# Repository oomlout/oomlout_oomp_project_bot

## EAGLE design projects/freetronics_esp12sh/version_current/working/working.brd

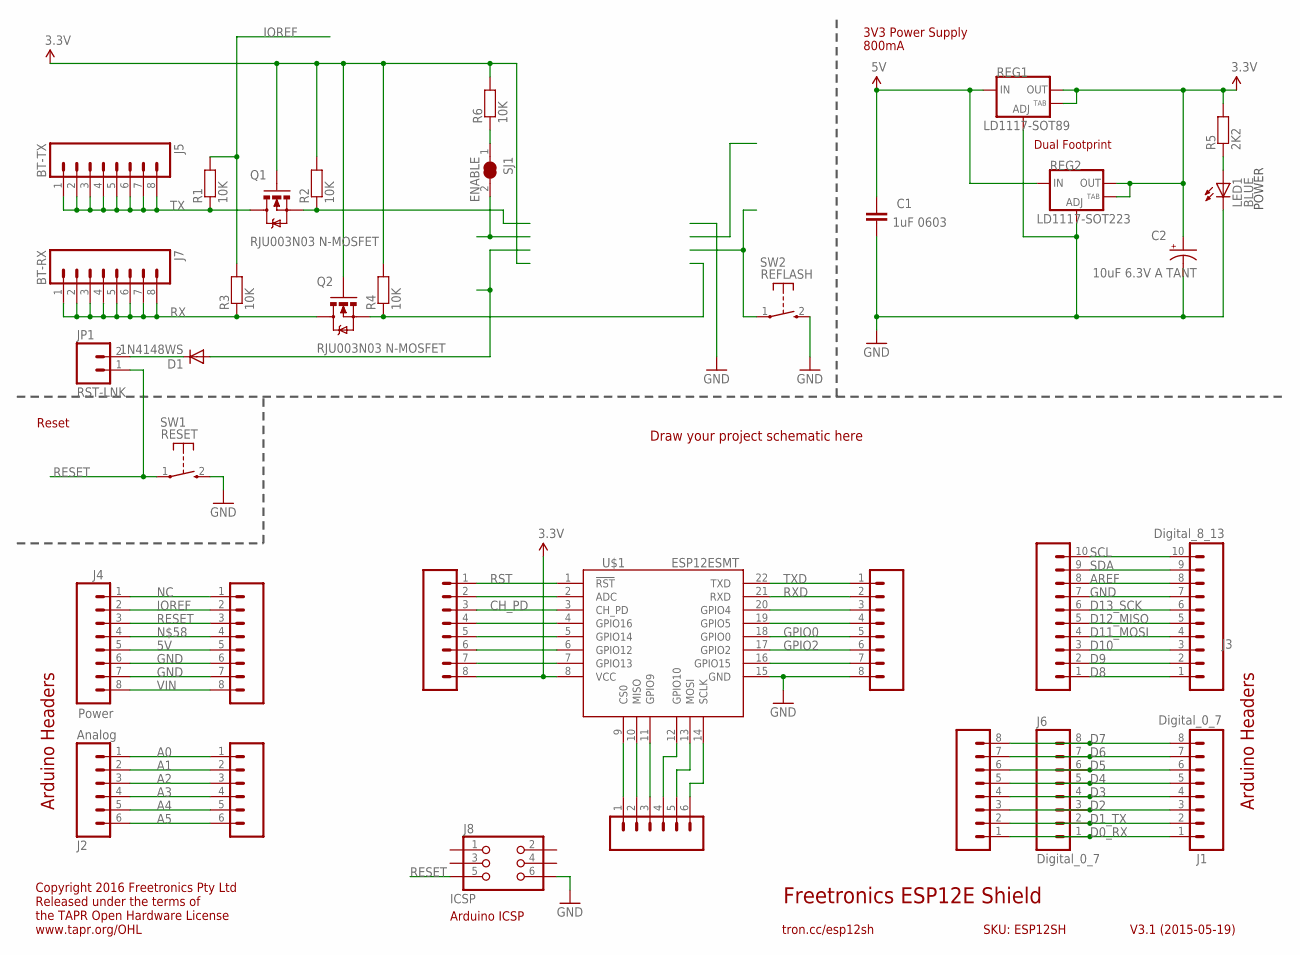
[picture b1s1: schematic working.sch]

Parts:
C1: 1uF 0603; 0603
C2: 10uF 6.3V A TANT; EIA3216
D1: 1N4148WS; SOD-323
J1, J6: Digital_0_7; 1X08
J2: Analog; 1X06
J3: Digital_8_13; 1X10
J4: Power; 1X08
J5: BT-TX; 1X08
J7: BT-RX; 1X08
J8: ICSP; 2X03PTH
JP1: RST-LNK; 1X02
LED1: BLUE; LED-0603
Q1, Q2: RJU003N03 N-MOSFET; SOT32-3
R1, R2, R3, R4, R6: 10K; 0603
R5: 2K2; 0603
REG1: LD1117-SOT89; SOT89
REG2: LD1117-SOT223; SOT223
SJ1: ENABLE; SJC
SL1: Digital_0_7; 1X08
SL2, SL7: Analog; 1X06
SL3: Digital_8_13; 1X10
SL4: Power; 1X08
SL5, SL6: 5V; 1X08
SW1: RESET; TACTILE_SWITCH_SMD_2PIN_TINY
SW2: REFLASH; TACTILE_SWITCH_SMD_2PIN_TINY
U$1: ESP12ESMT; ESP12E

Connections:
3.3V: C2.A (+), Q1.1 (G), Q2.1 (G), R2.2, R4.2, R5.2, R6.2, REG1.2 (OUT), REG1.4 (OUT), REG2.2 (OUT), REG2.4 (OUT), SL6.8, U$1.8 (VCC)
5V: C1.1, J4.5, REG1.3 (IN), REG2.3 (IN), SL4.5
A0: J2.1, SL2.1
A1: J2.2, SL2.2
A2: J2.3, SL2.3
A3: J2.4, SL2.4
A4: J2.5, SL2.5
A5: J2.6, SL2.6
AREF: J3.8, SL3.8
CH_PD: SJ1.2, SL6.3, U$1.3 (CH_PD)
D0_RX: J1.1, J6.1, SL1.1
D1_TX: J1.2, J6.2, SL1.2
D2: J1.3, J6.3, SL1.3
D3: J1.4, J6.4, SL1.4
D4: J1.5, J6.5, SL1.5
D5: J1.6, J6.6, SL1.6
D6: J1.7, J6.7, SL1.7
D7: J1.8, J6.8, SL1.8
D8: J3.1, SL3.1
D9: J3.2, SL3.2
D10: J3.3, SL3.3
D11_MOSI: J3.4, SL3.4
D12_MISO: J3.5, SL3.5
D13_SCK: J3.6, SL3.6
GND: C1.2, C2.C (-), J3.7, J4.6, J4.7, J8.6, LED1.C, REG1.1 (ADJ), REG2.1 (ADJ), SL3.7, SL4.6, SL4.7, SL5.8, SW1.2 (S), SW2.2 (S), U$1.15 (GND)
GPIO0: SL5.5, SW2.1, U$1.18 (GPIO0)
GPIO2: SL5.6, U$1.17 (GPIO2)
IOREF: J4.2, R1.2, R3.2, SL4.2
unnamed: SL7.1, U$1.9 (CS0)
unnamed: SL7.2, U$1.10 (MISO)
unnamed: SL7.3, U$1.11 (GPIO9)
unnamed: SL7.4, U$1.12 (GPIO10)
unnamed: LED1.A, R5.1
unnamed: SL7.5, U$1.13 (MOSI)
unnamed: SL7.6, U$1.14 (SCLK)
unnamed: SL5.7, U$1.16 (GPIO15)
unnamed: SL5.4, U$1.19 (GPIO5)
unnamed: SL5.3, U$1.20 (GPIO4)
unnamed: SL6.2, U$1.2 (ADC)
unnamed: SL6.4, U$1.4 (GPIO16)
unnamed: SL6.5, U$1.5 (GPIO14)
unnamed: SL6.6, U$1.6 (GPIO12)
unnamed: SL6.7, U$1.7 (GPIO13)
unnamed: J4.4, SL4.4
unnamed: R6.1, SJ1.1
unnamed: D1.1 (C), JP1.2
NC: J4.1, SL4.1
RESET: J4.3, J8.5, JP1.1, SL4.3, SW1.1
RST: D1.2 (A), SL6.1, U$1.1 (!RST)
RX: J7.1, J7.2, J7.3, J7.4, J7.5, J7.6, J7.7, J7.8, Q2.3 (D), R3.1
RXD: Q2.2 (S), R4.1, SL5.2, U$1.21 (RXD)
SCL: J3.10, SL3.10
SDA: J3.9, SL3.9
TX: J5.1, J5.2, J5.3, J5.4, J5.5, J5.6, J5.7, J5.8, Q1.3 (D), R1.1
TXD: Q1.2 (S), R2.1, SL5.1, U$1.22 (TXD)
VIN: J4.8, SL4.8

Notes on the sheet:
Freetronics ESP12E Shield
V3.1 (2015-05-19)
tron.cc/esp12sh
SKU: ESP12SH
Arduino Headers
Reset
Draw your project schematic here
Arduino ICSP
Copyright 2016 Freetronics Pty Ltd Released under the terms of the TAPR Open Hardware License www.tapr.org/OHL
POWER
3V3 Power Supply
Dual Footprint
800mA

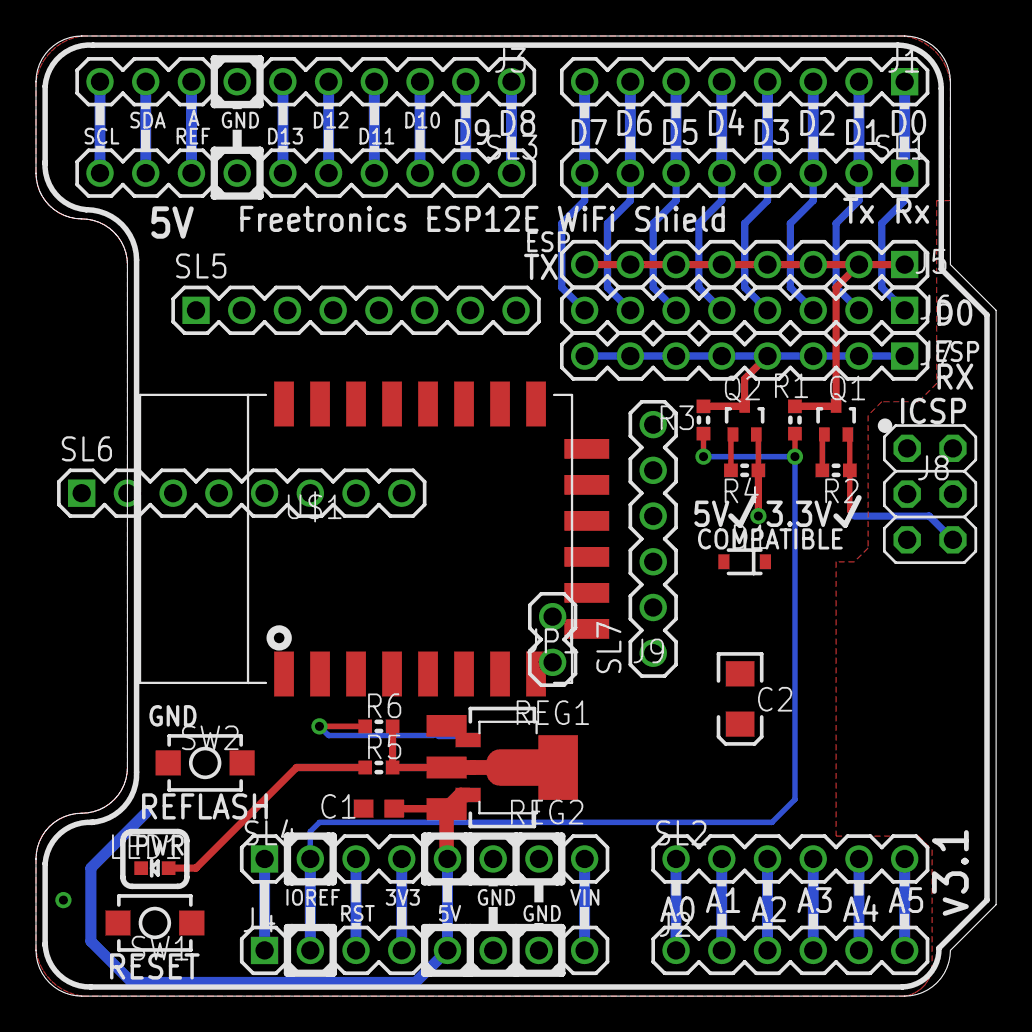
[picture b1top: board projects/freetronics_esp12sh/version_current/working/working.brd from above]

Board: 2 copper layers, 53.3 x 53.3 mm, 34 parts (1 on the bottom side), 56 nets.

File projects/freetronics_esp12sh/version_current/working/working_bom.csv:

"Id";"Designator";"Footprint";"Quantity";"Designation";"Supplier and ref";
1;"R3,R6,R1,R4,R2";"0603";5;"10K";;;
2;"SL6,SL5";"1X08";2;"5V";;;
3;"J2,SL2,SL7";"1X06";3;"Analog";;;
4;"R5";"0603";1;"2K2";;;
5;"J4,SL4";"1X08";2;"Power";;;
6;"C2";"EIA3216";1;"10uF 6.3V A TANT";;;
7;"SW2";"TACTILE_SWITCH_SMD_2PIN_TINY";1;"REFLASH";;;
8;"Q1,Q2";"SOT32-3";2;"RJU003N03 N-MOSFET";;;
9;"JP1";"1X02";1;"RST-LNK";;;
10;"J3,SL3";"1X10";2;"Digital_8_13";;;
11;"J1,SL1,J6";"1X08";3;"Digital_0_7";;;
12;"U$1";"ESP12E";1;"ESP12ESMT";;;
13;"REG1";"SOT89";1;"LD1117-SOT89";;;
14;"J5";"1X08";1;"BT-TX";;;
15;"D1";"SOD-323";1;"1N4148WS";;;
16;"C1";"0603";1;"1uF 0603";;;
17;"J8";"2X03PTH";1;"ICSP";;;
18;"SW1";"TACTILE_SWITCH_SMD_2PIN_TINY";1;"RESET";;;
19;"J7";"1X08";1;"BT-RX";;;
20;"LED1";"LED-0603";1;"BLUE";;;
21;"REG2";"SOT223";1;"LD1117-SOT223";;;
22;"SJ1";"SJC";1;"ENABLE";;;

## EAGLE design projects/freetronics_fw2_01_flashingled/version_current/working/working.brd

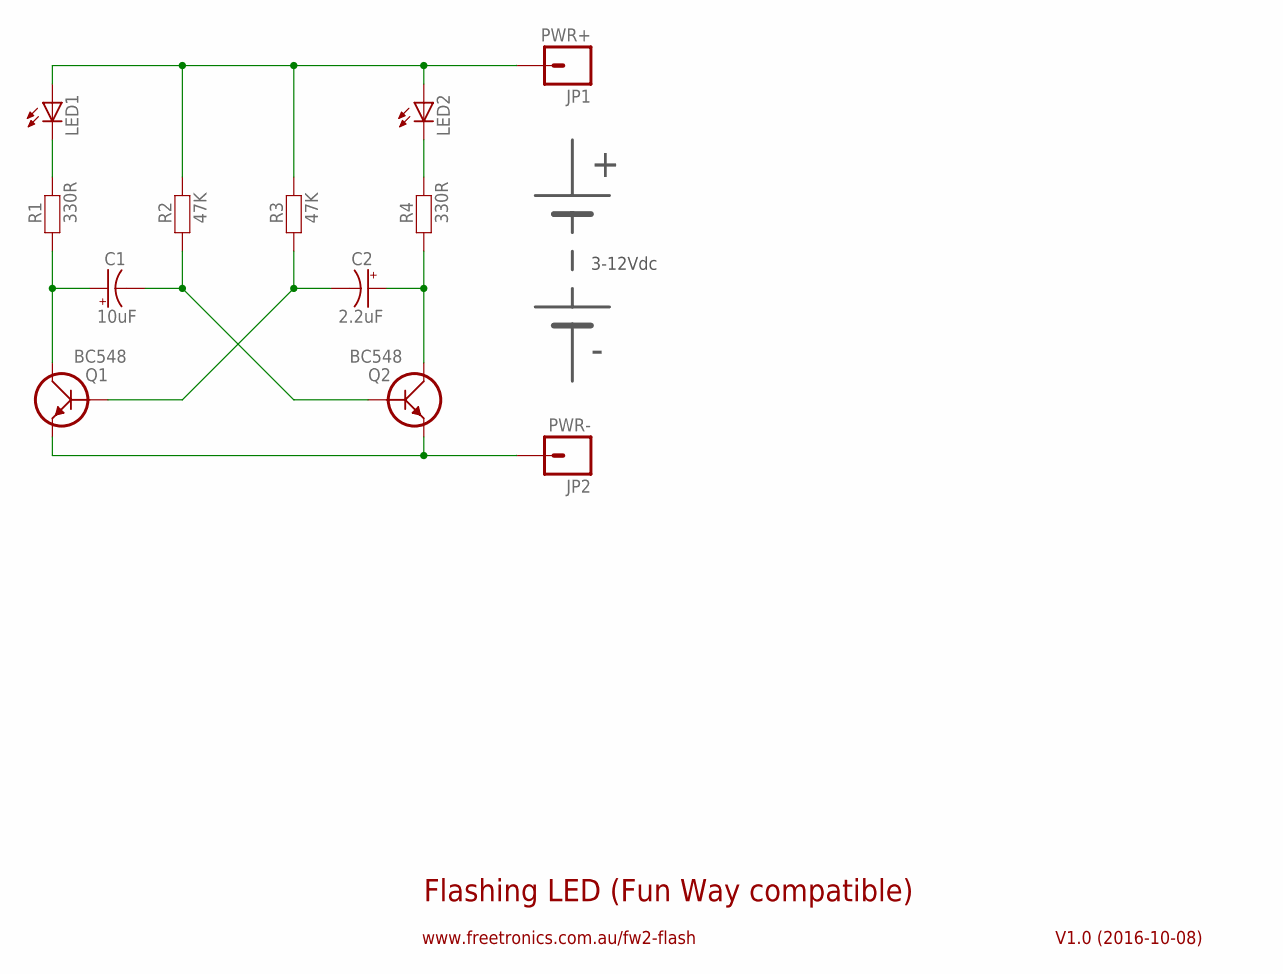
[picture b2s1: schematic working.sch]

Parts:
C1: 10uF; E5-5
C2: 2.2uF; E5-5
JP1: PWR+; 1X01
JP2: PWR-; 1X01
LED1, LED2: LED5MML; LED5MMLARGE
Q1, Q2: BC548; TO-92
R1, R4: 330R; AXIAL-0.4-LARGE
R2, R3: 47K; AXIAL-0.4-LARGE

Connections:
unnamed: LED1.K (C), R1.P$2 (2)
unnamed: JP1.1, LED1.A, LED2.A, R2.P$2 (2), R3.P$2 (2)
unnamed: C1.+, Q1.1 (C), R1.P$1 (1)
unnamed: C2.+, Q2.1 (C), R4.P$1 (1)
unnamed: LED2.K (C), R4.P$2 (2)
unnamed: C2.-, Q1.2 (B), R3.P$1 (1)
unnamed: C1.-, Q2.2 (B), R2.P$1 (1)
unnamed: JP2.1, Q1.3 (E), Q2.3 (E)

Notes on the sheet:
Flashing LED (Fun Way compatible)
V1.0 (2016-10-08)
www.freetronics.com.au/fw2-flash
3-12Vdc

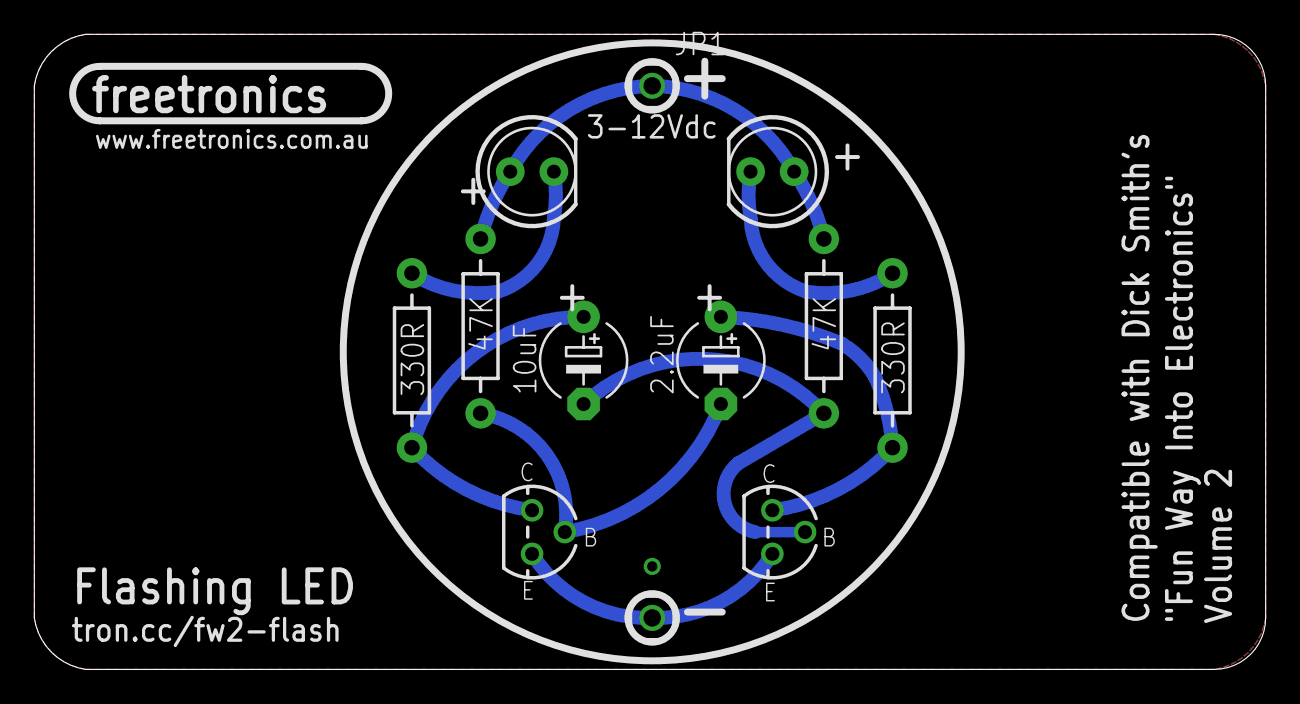
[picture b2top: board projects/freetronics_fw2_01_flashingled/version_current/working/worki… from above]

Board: 2 copper layers, 71.7 x 37.0 mm, 12 parts (0 on the bottom side), 8 nets.

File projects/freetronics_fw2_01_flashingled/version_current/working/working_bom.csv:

"Id";"Designator";"Footprint";"Quantity";"Designation";"Supplier and ref";
1;"C1";"E5-5";1;"10uF";;;
2;"Q1,Q2";"TO-92";2;"BC548";;;
3;"R3,R2";"AXIAL-0.4-LARGE";2;"47K";;;
4;"R4,R1";"AXIAL-0.4-LARGE";2;"330R";;;
5;"LED1,LED2";"LED5MMLARGE";2;"";;;
6;"JP1";"1X01";1;"PWR+";;;
7;"C2";"E5-5";1;"2.2uF";;;
8;"JP2";"1X01";1;"PWR-";;;

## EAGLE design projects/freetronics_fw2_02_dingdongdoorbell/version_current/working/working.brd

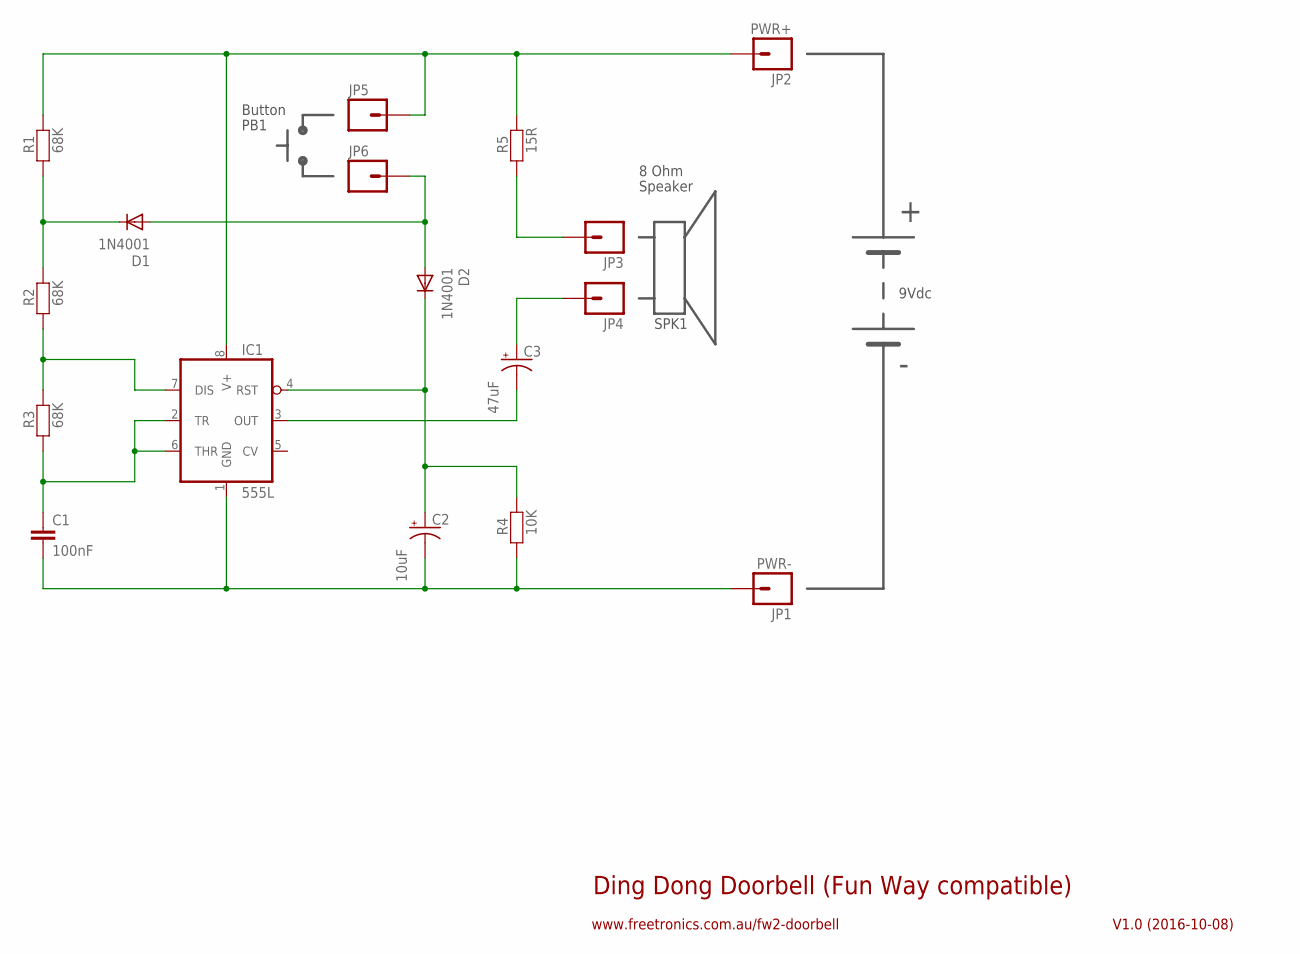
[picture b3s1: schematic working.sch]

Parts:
C1: 100nF; CAP-PTH-SMALL
C2: 10uF; CPOL-RADIAL-10UF-25V
C3: 47uF; CPOL-RADIAL-10UF-25V
D1, D2: 1N4001; DIODE-1N4001
IC1: 555L; DIL08L
JP1, JP5, JP6: PWR-; 1X01
JP2: PWR+; 1X01
JP3: SPKR+; 1X01
JP4: SPKR-; 1X01
R1, R2, R3: 68K; AXIAL-0.4-LARGE
R4: 10K; AXIAL-0.4-LARGE
R5: 15R; AXIAL-0.4-LARGE

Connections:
unnamed: D1.C, R1.P$1 (1), R2.P$2 (2)
unnamed: IC1.7 (DIS), R2.P$1 (1), R3.P$2 (2)
unnamed: D1.A, D2.A, JP6.1
unnamed: IC1.8 (V+), JP2.1, JP5.1, R1.P$2 (2), R5.P$2 (2)
unnamed: JP3.1, R5.P$1 (1)
unnamed: C3.1 (+), JP4.1
unnamed: C3.2 (-), IC1.3 (OUT)
unnamed: C2.1 (+), D2.C, IC1.4 (RST), R4.P$2 (2)
unnamed: C1.2, C2.2 (-), IC1.1 (GND), JP1.1, R4.P$1 (1)
unnamed: C1.1, IC1.2 (TR), IC1.6 (THR), R3.P$1 (1)

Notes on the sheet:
Ding Dong Doorbell (Fun Way compatible)
V1.0 (2016-10-08)
www.freetronics.com.au/fw2-doorbell
9Vdc
8 Ohm
Speaker
Button
PB1
SPK1

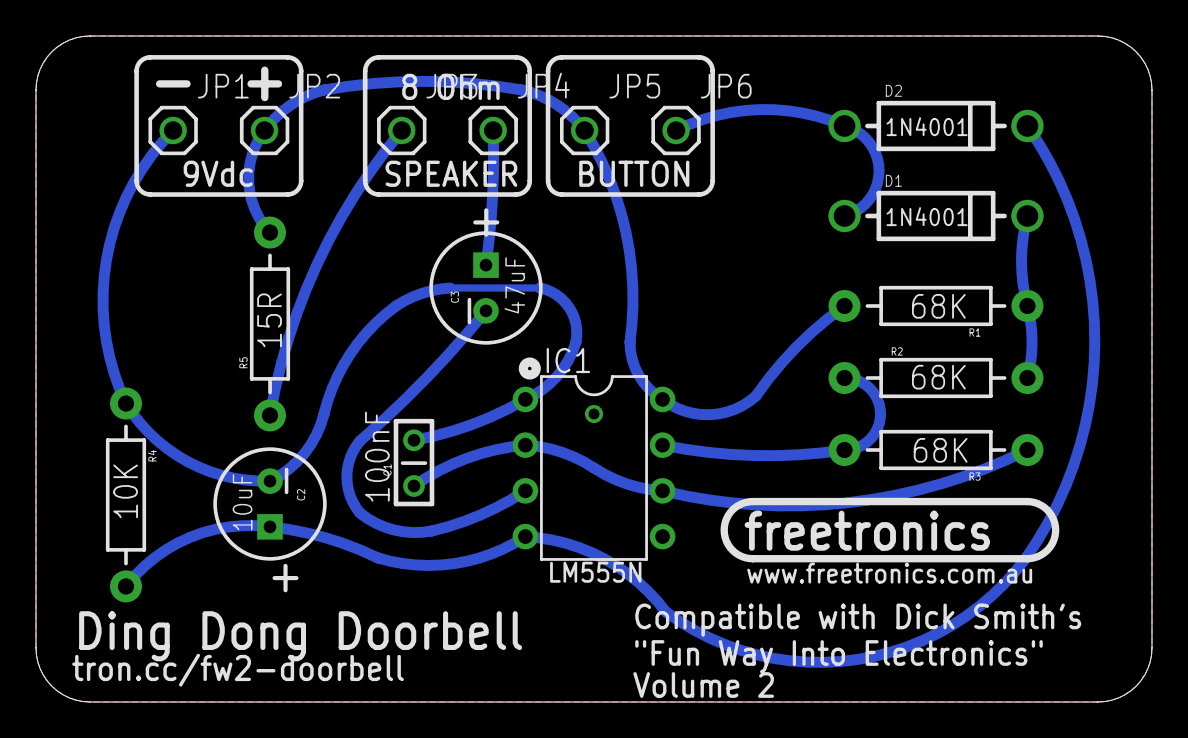
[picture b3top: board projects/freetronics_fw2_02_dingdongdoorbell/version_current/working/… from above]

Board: 2 copper layers, 62.0 x 37.0 mm, 17 parts (0 on the bottom side), 10 nets.

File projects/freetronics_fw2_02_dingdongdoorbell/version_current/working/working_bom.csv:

"Id";"Designator";"Footprint";"Quantity";"Designation";"Supplier and ref";
1;"JP5,JP1,JP6";"1X01";3;"PWR-";;;
2;"C2";"CPOL-RADIAL-10UF-25V";1;"10uF";;;
3;"D2,D1";"DIODE-1N4001";2;"1N4001";;;
4;"C1";"CAP-PTH-SMALL";1;"100nF";;;
5;"IC1";"DIL08L";1;"555L";;;
6;"JP3";"1X01";1;"SPKR+";;;
7;"JP2";"1X01";1;"PWR+";;;
8;"R3,R1,R2";"AXIAL-0.4-LARGE";3;"68K";;;
9;"C3";"CPOL-RADIAL-10UF-25V";1;"47uF";;;
10;"JP4";"1X01";1;"SPKR-";;;
11;"R5";"AXIAL-0.4-LARGE";1;"15R";;;
12;"R4";"AXIAL-0.4-LARGE";1;"10K";;;

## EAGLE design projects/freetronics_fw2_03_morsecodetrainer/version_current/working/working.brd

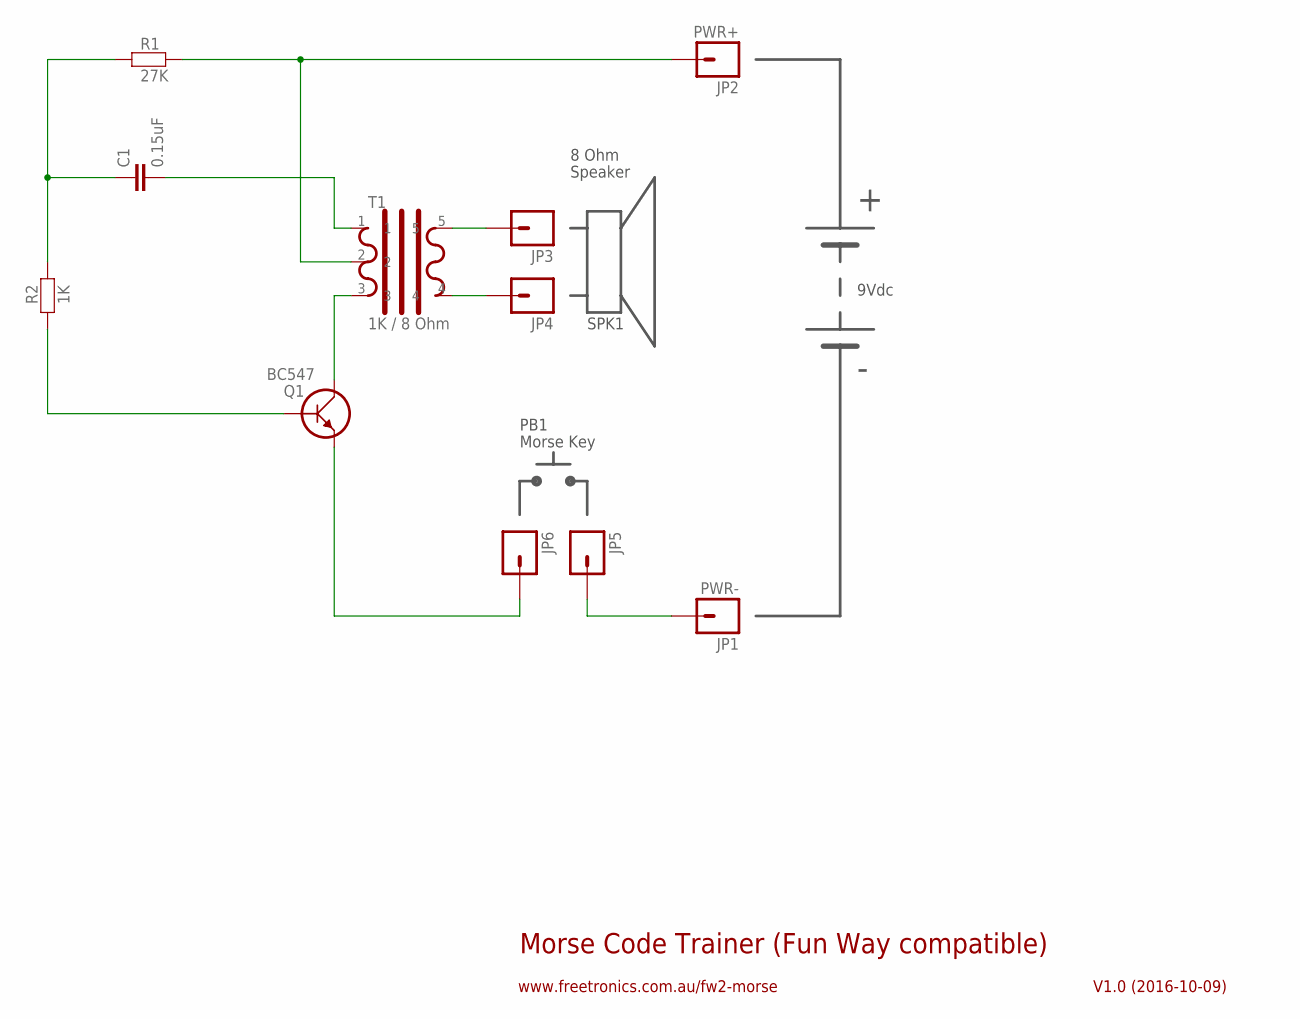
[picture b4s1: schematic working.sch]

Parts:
C1: 0.15uF; CAP-PTH-SMALL
JP1, JP5, JP6: PWR-; 1X01
JP2: PWR+; 1X01
JP3: SPKR+; 1X01
JP4: SPKR-; 1X01
Q1: BC547; TO-92
R1: 27K; FREETRONICS_AXIAL-0.4
R2: 1K; FREETRONICS_AXIAL-0.4
T1: 1K / 8 Ohm; TRANS350MW

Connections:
unnamed: JP4.1, T1.4
unnamed: JP3.1, T1.5
unnamed: JP2.1, R1.P$2 (2), T1.2
unnamed: C1.2, T1.1
unnamed: Q1.1 (C), T1.3
unnamed: JP1.1, JP5.1
unnamed: JP6.1, Q1.3 (E)
unnamed: Q1.2 (B), R2.P$1 (1)
unnamed: C1.1, R1.P$1 (1), R2.P$2 (2)

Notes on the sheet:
Morse Code Trainer (Fun Way compatible)
V1.0 (2016-10-09)
www.freetronics.com.au/fw2-morse
9Vdc
8 Ohm
Speaker
Morse Key
PB1
SPK1

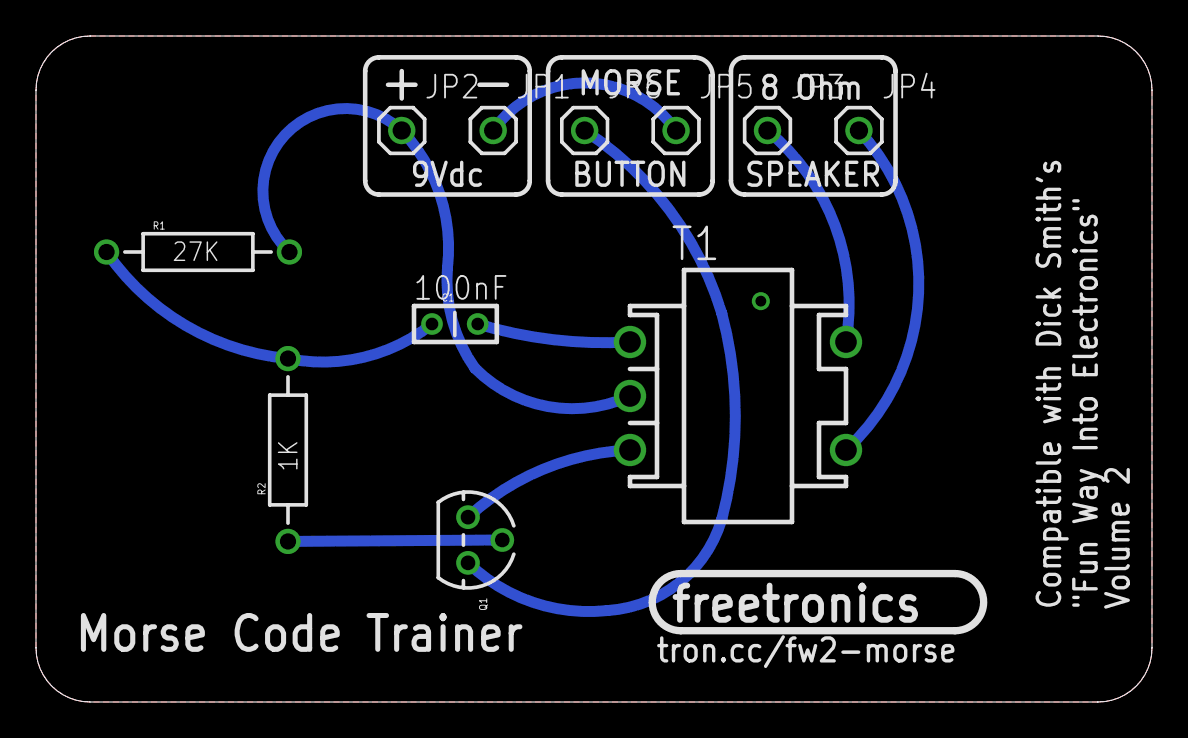
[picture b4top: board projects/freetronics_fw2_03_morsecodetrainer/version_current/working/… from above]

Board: 2 copper layers, 62.0 x 37.0 mm, 11 parts (0 on the bottom side), 9 nets.

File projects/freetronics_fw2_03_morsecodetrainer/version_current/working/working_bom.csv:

"Id";"Designator";"Footprint";"Quantity";"Designation";"Supplier and ref";
1;"JP3";"1X01";1;"SPKR+";;;
2;"T1";"TRANS350MW";1;"1K / 8 Ohm";;;
3;"JP2";"1X01";1;"PWR+";;;
4;"C1";"CAP-PTH-SMALL";1;"0.15uF";;;
5;"R2";"FREETRONICS_AXIAL-0.4";1;"1K";;;
6;"R1";"FREETRONICS_AXIAL-0.4";1;"27K";;;
7;"Q1";"TO-92";1;"BC547";;;
8;"JP6,JP5,JP1";"1X01";3;"PWR-";;;
9;"JP4";"1X01";1;"SPKR-";;;

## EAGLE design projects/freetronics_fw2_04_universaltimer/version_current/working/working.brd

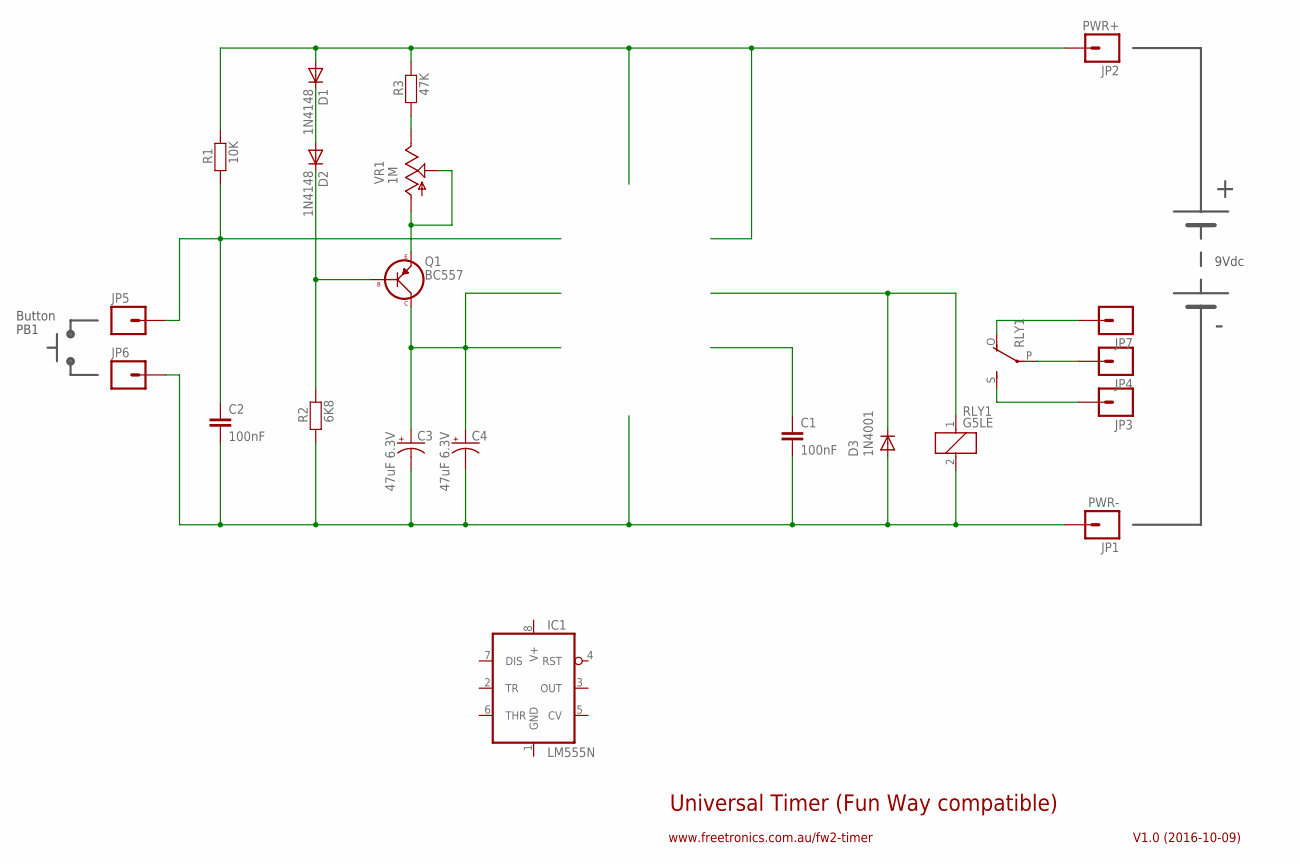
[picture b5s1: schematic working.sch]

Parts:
C1, C2: 100nF; CAP-PTH-SMALL
C3, C4: 47uF 6.3V; CPOL-RADIAL-10UF-25V
D1, D2: 1N4148; DIODE-1N914
D3: 1N4001; DIODE-1N4001
IC1: LM555N; DIL08
JP1, JP5, JP6: PWR-; 1X01
JP2: PWR+; 1X01
JP3: SPKR+; 1X01
JP4, JP7: SPKR-; 1X01
Q1: BC557; TO-92
R1: 10K; FREETRONICS_AXIAL-0.4
R2: 6K8; FREETRONICS_AXIAL-0.4
R3: 47K; FREETRONICS_AXIAL-0.4
RLY1: G5LE
VR1: 1M; 6MM

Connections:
GND: IC1.1 (GND)
unnamed: C3.1 (+), C4.1 (+), Q1.1 (C)
unnamed: C1.2, C2.2, C3.2 (-), C4.2 (-), D3.A, JP1.1, JP6.1, R2.P$1 (1), RLY1.2
unnamed: D3.C, RLY1.1
unnamed: JP4.1, RLY1.P
unnamed: JP3.1, RLY1.S
unnamed: JP7.1, RLY1.O
unnamed: C2.1, JP5.1, R1.P$1 (1)
unnamed: D2.C, Q1.2 (B), R2.P$2 (2)
unnamed: Q1.3 (E), VR1.A, VR1.S
unnamed: D1.A, JP2.1, R1.P$2 (2), R3.P$2 (2)
unnamed: R3.P$1 (1), VR1.E
unnamed: D1.C, D2.A
V+: IC1.8 (V+)

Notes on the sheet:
Universal Timer (Fun Way compatible)
V1.0 (2016-10-09)
www.freetronics.com.au/fw2-timer
9Vdc
Button
PB1

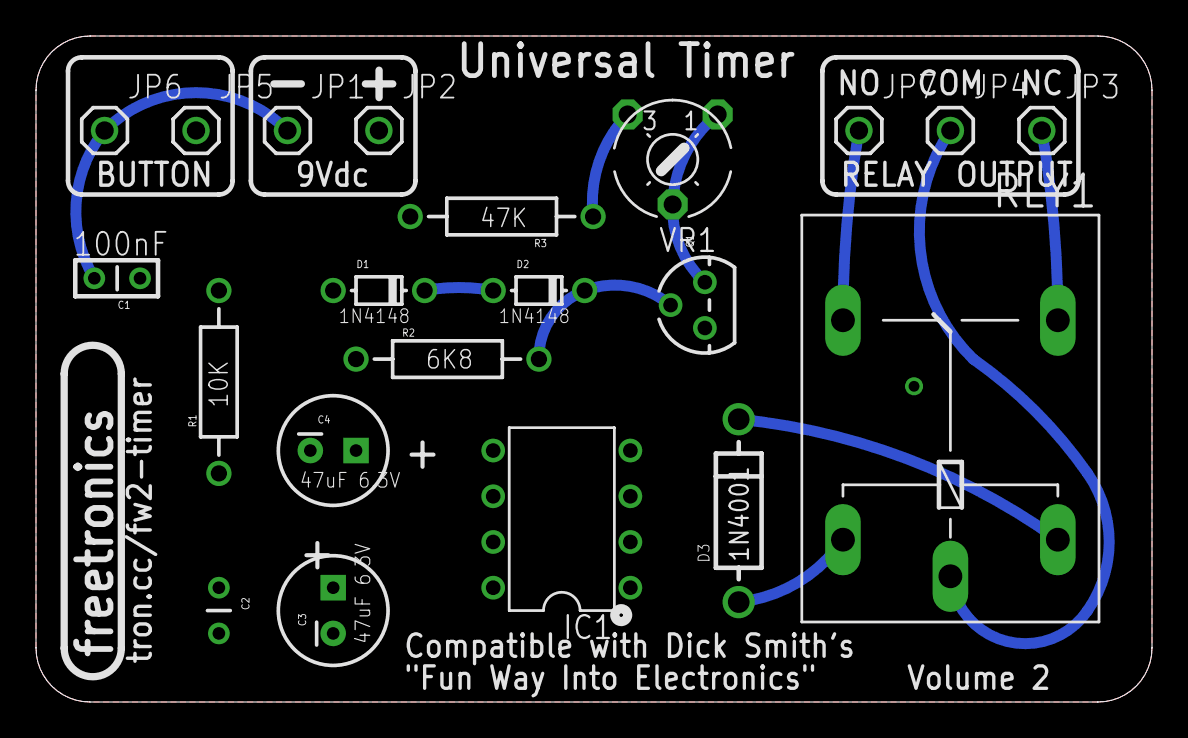
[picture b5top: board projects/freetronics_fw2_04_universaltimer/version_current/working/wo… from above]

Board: 2 copper layers, 62.0 x 37.0 mm, 21 parts (0 on the bottom side), 12 nets.

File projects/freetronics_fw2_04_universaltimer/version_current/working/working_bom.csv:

"Id";"Designator";"Footprint";"Quantity";"Designation";"Supplier and ref";
1;"C1,C2";"CAP-PTH-SMALL";2;"100nF";;;
2;"JP6,JP5,JP1";"1X01";3;"PWR-";;;
3;"D3";"DIODE-1N4001";1;"1N4001";;;
4;"JP2";"1X01";1;"PWR+";;;
5;"D1,D2";"DIODE-1N914";2;"1N4148";;;
6;"JP3";"1X01";1;"SPKR+";;;
7;"VR1";"6MM";1;"1M";;;
8;"JP4,JP7";"1X01";2;"SPKR-";;;
9;"R3";"FREETRONICS_AXIAL-0.4";1;"47K";;;
10;"R2";"FREETRONICS_AXIAL-0.4";1;"6K8";;;
11;"C3,C4";"CPOL-RADIAL-10UF-25V";2;"47uF 6.3V";;;
12;"IC1";"DIL08";1;"LM555N";;;
13;"R1";"FREETRONICS_AXIAL-0.4";1;"10K";;;
14;"Q1";"TO-92";1;"BC557";;;
15;"RLY1";"G5LE";1;"G5LE";;;

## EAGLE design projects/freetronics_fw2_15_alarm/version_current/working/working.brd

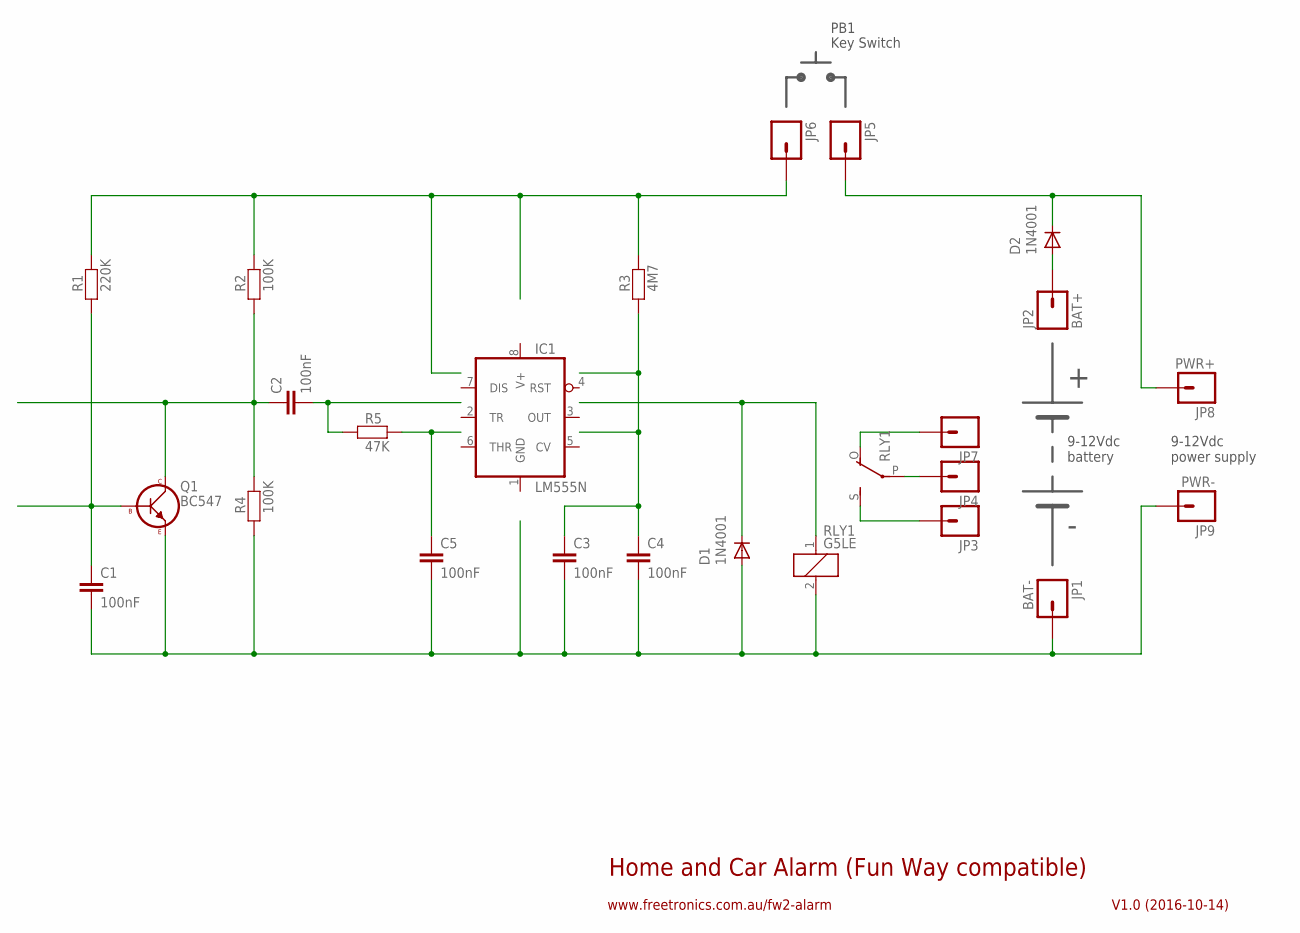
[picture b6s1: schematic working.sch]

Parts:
C1, C2, C3, C4, C5: 100nF; CAP-PTH-SMALL
D1, D2: 1N4001; DIODE-1N4001
IC1: LM555N; DIL08
JP1: BAT-; 1X01
JP2: BAT+; 1X01
JP3: SPKR+; 1X01
JP4, JP7: SPKR-; 1X01
JP5, JP6, JP9: PWR-; 1X01
JP8: PWR+; 1X01
Q1: BC547; TO-92
R1: 220K; FREETRONICS_AXIAL-0.4
R2, R4: 100K; FREETRONICS_AXIAL-0.4
R3: 4M7; FREETRONICS_AXIAL-0.4
R5: 47K; FREETRONICS_AXIAL-0.4
RLY1: G5LE

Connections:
GND: IC1.1 (GND)
unnamed: C3.1, C4.1, R3.P$1 (1)
unnamed: C1.2, C3.2, C4.2, C5.2, D1.A, JP1.1, JP9.1, Q1.3 (E), R4.P$1 (1), RLY1.2
unnamed: D1.C, RLY1.1
unnamed: JP6.1, R1.P$2 (2), R2.P$2 (2), R3.P$2 (2)
unnamed: JP4.1, RLY1.P
unnamed: JP3.1, RLY1.S
unnamed: JP7.1, RLY1.O
unnamed: C5.1, R5.P$2 (2)
unnamed: C1.1, Q1.2 (B), R1.P$1 (1)
unnamed: C2.1, Q1.1 (C), R2.P$1 (1), R4.P$2 (2)
unnamed: C2.2, R5.P$1 (1)
unnamed: D2.A, JP2.1
unnamed: D2.C, JP5.1, JP8.1
V+: IC1.8 (V+)

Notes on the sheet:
Home and Car Alarm (Fun Way compatible)
V1.0 (2016-10-14)
www.freetronics.com.au/fw2-alarm
9-12Vdc battery
Key Switch
PB1
9-12Vdc power supply

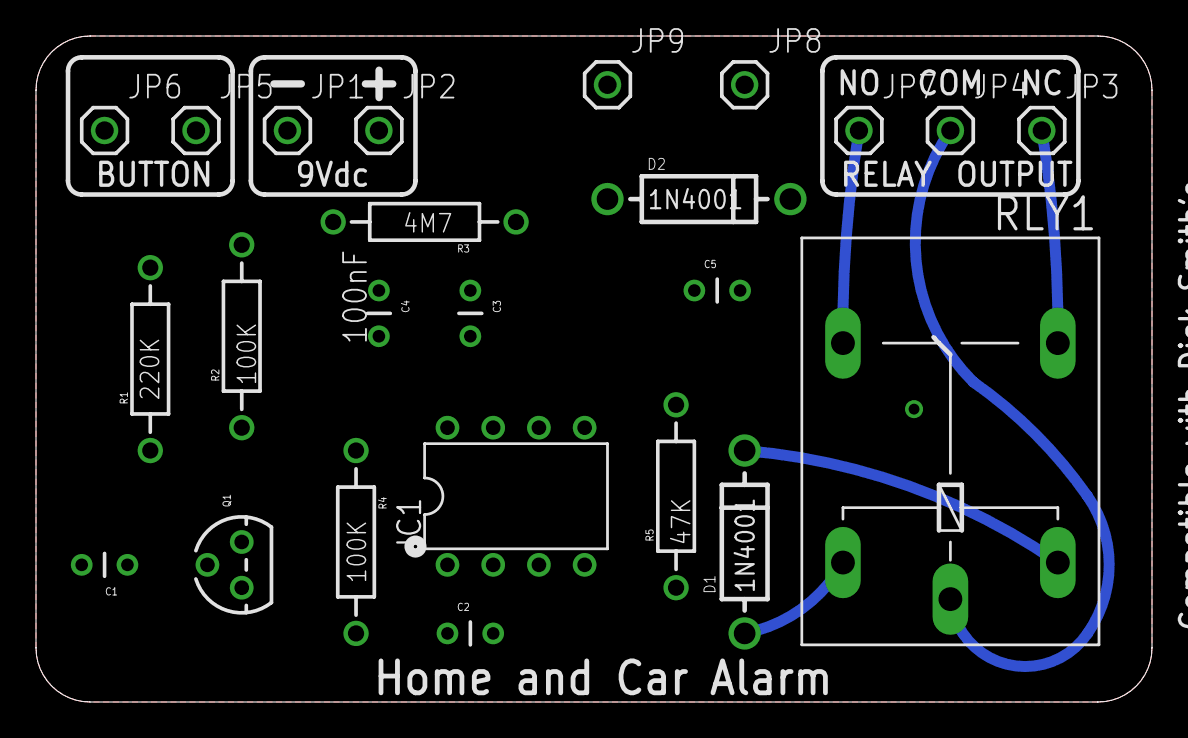
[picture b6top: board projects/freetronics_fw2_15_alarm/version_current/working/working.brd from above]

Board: 2 copper layers, 62.0 x 37.0 mm, 24 parts (0 on the bottom side), 13 nets.

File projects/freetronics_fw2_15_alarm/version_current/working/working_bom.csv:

"Id";"Designator";"Footprint";"Quantity";"Designation";"Supplier and ref";
1;"R3";"FREETRONICS_AXIAL-0.4";1;"4M7";;;
2;"JP5,JP9,JP6";"1X01";3;"PWR-";;;
3;"C2,C4,C1,C5,C3";"CAP-PTH-SMALL";5;"100nF";;;
4;"R2,R4";"FREETRONICS_AXIAL-0.4";2;"100K";;;
5;"R1";"FREETRONICS_AXIAL-0.4";1;"220K";;;
6;"JP7,JP4";"1X01";2;"SPKR-";;;
7;"JP1";"1X01";1;"BAT-";;;
8;"JP3";"1X01";1;"SPKR+";;;
9;"IC1";"DIL08";1;"LM555N";;;
10;"R5";"FREETRONICS_AXIAL-0.4";1;"47K";;;
11;"Q1";"TO-92";1;"BC547";;;
12;"D2,D1";"DIODE-1N4001";2;"1N4001";;;
13;"JP2";"1X01";1;"BAT+";;;
14;"RLY1";"G5LE";1;"G5LE";;;
15;"JP8";"1X01";1;"PWR+";;;

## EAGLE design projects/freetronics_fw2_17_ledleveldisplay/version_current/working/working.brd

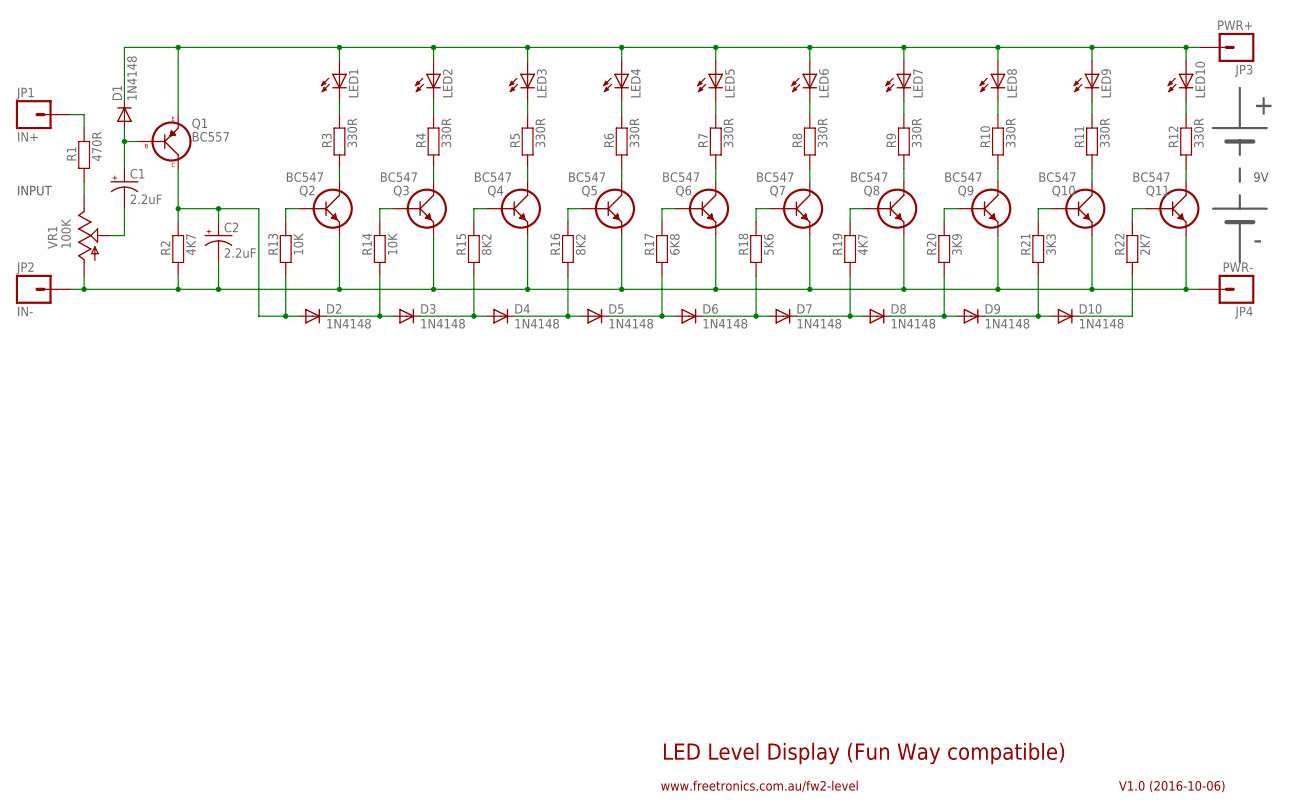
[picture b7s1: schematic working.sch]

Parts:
C1, C2: 2.2uF; CPOL-RADIAL-100UF-25V
D1, D2, D3, D4, D5, D6, D7, D8, D9, D10: 1N4148; DIODE-1N914L
JP1: IN+; 1X01
JP2: IN-; 1X01
JP3: PWR+; 1X01
JP4: PWR-; 1X01
LED1, LED2, LED3, LED4, LED5, LED6, LED7, LED8, LED9, LED10: LED5MML; LED5MMLARGE
Q1: BC557; TO-92
Q2, Q3, Q4, Q5, Q6, Q7, Q8, Q9, Q10, Q11: BC547; TO-92
R1: 470R; AXIAL-0.4-LARGE
R2: 4K7; AXIAL-0.4-LARGE
R3, R4, R5, R6, R7, R8, R9, R10, R11, R12: 330R; 0309VW
R13, R14: 10K; 0309VW
R15, R16: 8K2; 0309VW
R17: 6K8; 0309VW
R18: 5K6; 0309VW
R19: 4K7; 0309VW
R20: 3K9; 0309VW
R21: 3K3; 0309VW
R22: 2K7; 0309VW
VR1: 100K; 6MM

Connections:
unnamed: D10.C, R22.1
unnamed: Q2.2 (B), R13.2
unnamed: Q2.1 (C), R3.2
unnamed: LED1.K (C), R3.1
unnamed: Q11.2 (B), R22.2
unnamed: D1.C, JP3.1, LED1.A, LED2.A, LED3.A, LED4.A, LED5.A, LED6.A, LED7.A, LED8.A, LED9.A, LED10.A, Q1.3 (E)
unnamed: Q3.1 (C), R4.2
unnamed: LED2.K (C), R4.1
unnamed: Q4.1 (C), R5.2
unnamed: D6.C, D7.A, R18.1
unnamed: LED3.K (C), R5.1
unnamed: Q3.2 (B), R14.2
unnamed: C2.1 (+), D2.A, Q1.1 (C), R2.P$2 (2), R13.1
unnamed: D2.C, D3.A, R14.1
unnamed: C2.2 (-), JP2.1, JP4.1, Q2.3 (E), Q3.3 (E), Q4.3 (E), Q5.3 (E), Q6.3 (E), Q7.3 (E), Q8.3 (E), Q9.3 (E), Q10.3 (E), Q11.3 (E), R2.P$1 (1), VR1.A
unnamed: Q5.1 (C), R6.2
unnamed: LED4.K (C), R6.1
unnamed: Q6.1 (C), R7.2
unnamed: LED5.K (C), R7.1
unnamed: Q7.1 (C), R8.2
unnamed: LED6.K (C), R8.1
unnamed: Q4.2 (B), R15.2
unnamed: Q5.2 (B), R16.2
unnamed: Q6.2 (B), R17.2
unnamed: D5.C, D6.A, R17.1
unnamed: D4.C, D5.A, R16.1
unnamed: D3.C, D4.A, R15.1
unnamed: D7.C, D8.A, R19.1
unnamed: D8.C, D9.A, R20.1
unnamed: D9.C, D10.A, R21.1
unnamed: Q7.2 (B), R18.2
unnamed: Q8.2 (B), R19.2
unnamed: Q9.2 (B), R20.2
unnamed: Q10.2 (B), R21.2
unnamed: Q8.1 (C), R9.2
unnamed: LED7.K (C), R9.1
unnamed: Q9.1 (C), R10.2
unnamed: LED8.K (C), R10.1
unnamed: Q10.1 (C), R11.2
unnamed: LED9.K (C), R11.1
unnamed: Q11.1 (C), R12.2
unnamed: LED10.K (C), R12.1
unnamed: C1.1 (+), D1.A, Q1.2 (B)
unnamed: C1.2 (-), VR1.S
unnamed: R1.P$1 (1), VR1.E
unnamed: JP1.1, R1.P$2 (2)

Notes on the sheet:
LED Level Display (Fun Way compatible)
V1.0 (2016-10-06)
www.freetronics.com.au/fw2-level
INPUT

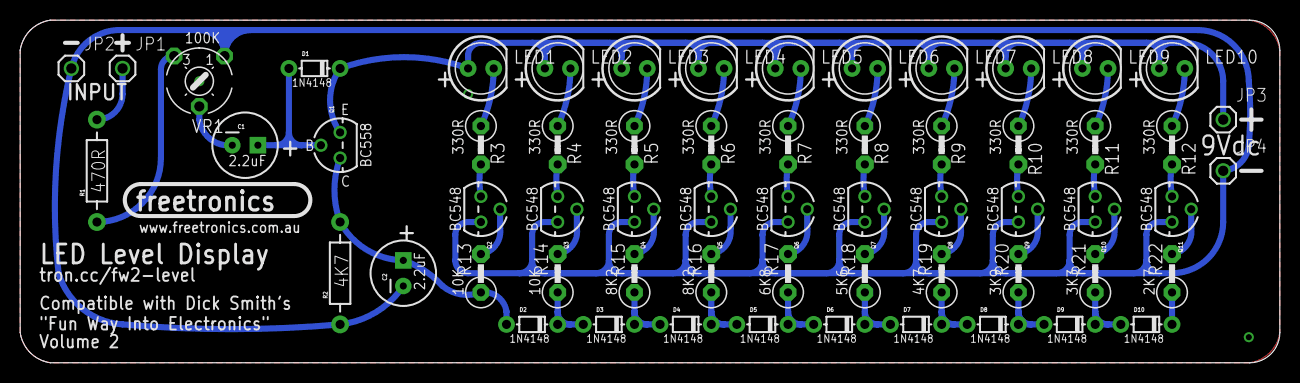
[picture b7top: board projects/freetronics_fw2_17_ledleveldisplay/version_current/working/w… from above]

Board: 2 copper layers, 125.0 x 34.0 mm, 60 parts (0 on the bottom side), 46 nets.

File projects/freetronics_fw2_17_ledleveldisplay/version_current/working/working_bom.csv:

"Id";"Designator";"Footprint";"Quantity";"Designation";"Supplier and ref";
1;"Q4,Q2,Q6,Q9,Q8,Q3,Q7,Q10,Q5,Q11";"TO-92";10;"BC547";;;
2;"C2,C1";"CPOL-RADIAL-100UF-25V";2;"2.2uF";;;
3;"D4,D2,D1,D10,D5,D9,D8,D3,D6,D7";"DIODE-1N914L";10;"1N4148";;;
4;"R16,R15";"0309VW";2;"8K2";;;
5;"LED1,LED8,LED2,LED3,LED4,LED7,LED9,LED10,LED6,LED5";"LED5MMLARGE";10;"";;;
6;"JP2";"1X01";1;"IN-";;;
7;"R11,R10,R3,R7,R9,R8,R6,R4,R5,R12";"0309VW";10;"330R";;;
8;"R13,R14";"0309VW";2;"10K";;;
9;"R17";"0309VW";1;"6K8";;;
10;"R21";"0309VW";1;"3K3";;;
11;"R1";"AXIAL-0.4-LARGE";1;"470R";;;
12;"R19";"0309VW";1;"4K7";;;
13;"R20";"0309VW";1;"3K9";;;
14;"JP3";"1X01";1;"PWR+";;;
15;"JP4";"1X01";1;"PWR-";;;
16;"Q1";"TO-92";1;"BC557";;;
17;"VR1";"6MM";1;"100K";;;
18;"R18";"0309VW";1;"5K6";;;
19;"R2";"AXIAL-0.4-LARGE";1;"4K7";;;
20;"R22";"0309VW";1;"2K7";;;
21;"JP1";"1X01";1;"IN+";;;

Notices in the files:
projects/freetronics_esp12sh/version_current/working/working.brd:
(c) 2015 Freetronics Pty Ltd
Open Hardware License
projects/freetronics_fw2_01_flashingled/version_current/working/working.brd:
(c) 2016 Freetronics Pty Ltd
Licensed under the TAPR
